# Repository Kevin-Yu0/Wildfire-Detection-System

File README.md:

# Wildfire-Detection-System
This is the codebase for the Wildfire Detection System Project
Computer Engineering Senior Capstone 2025-2026
Contributors:
    Kevin Yu
    Manny Lemus
    Jake Gilbert
    Aliston Ma
    Frank Xiao

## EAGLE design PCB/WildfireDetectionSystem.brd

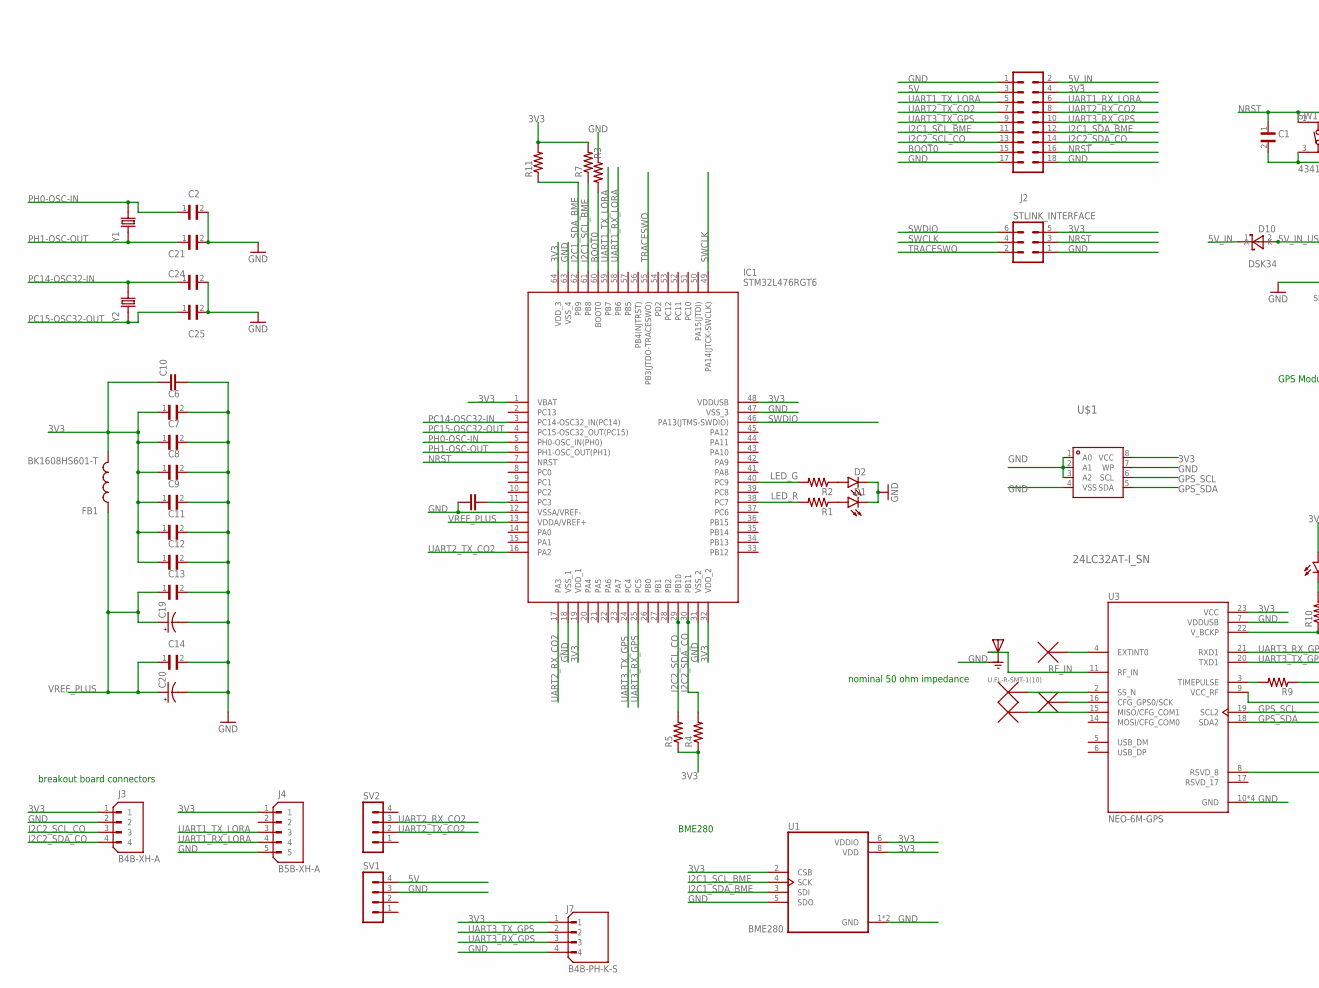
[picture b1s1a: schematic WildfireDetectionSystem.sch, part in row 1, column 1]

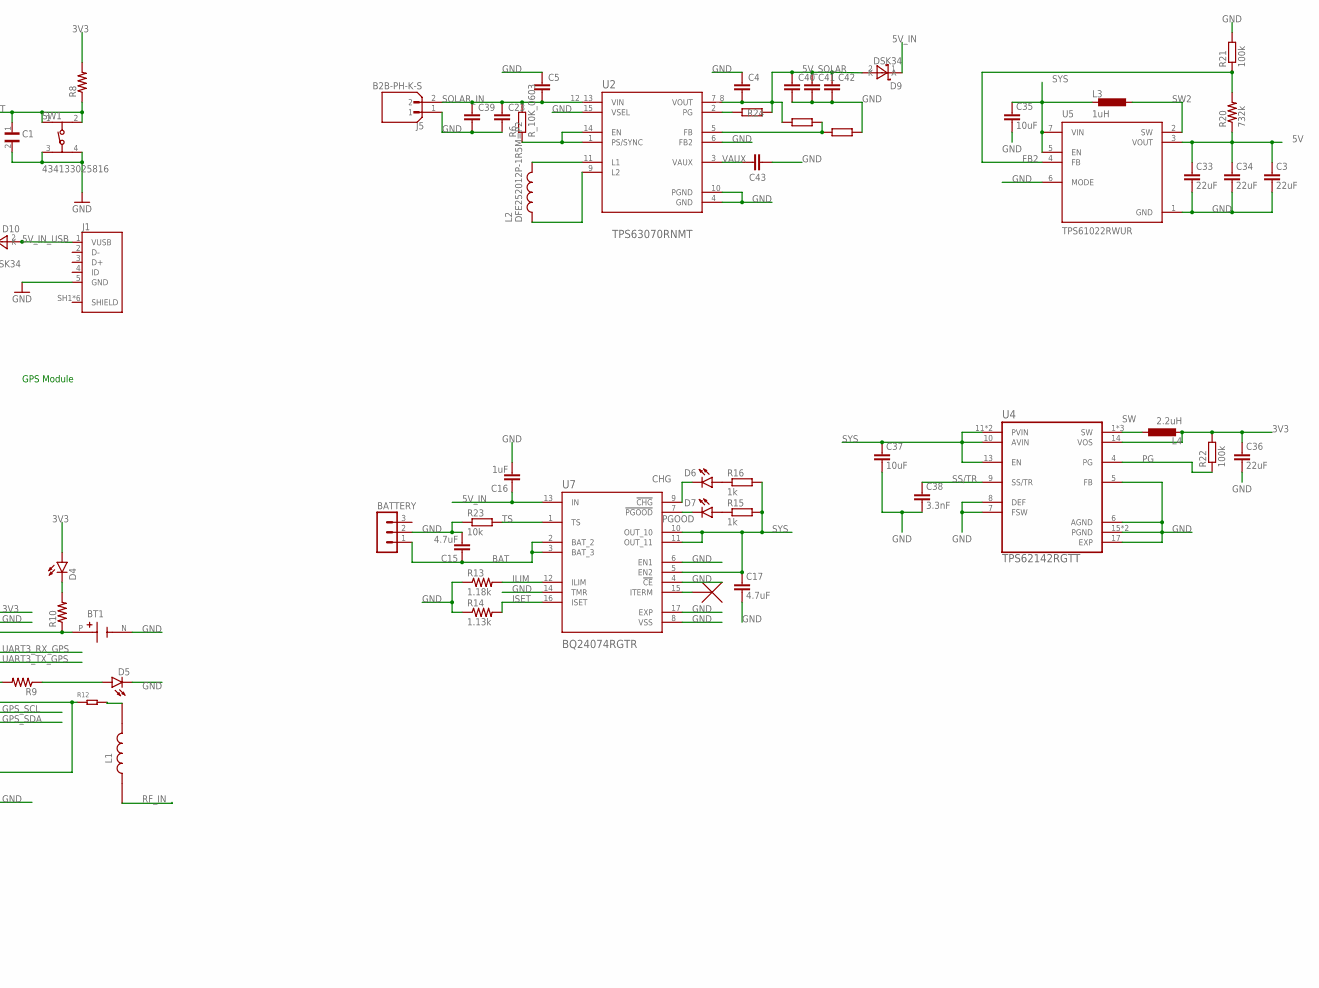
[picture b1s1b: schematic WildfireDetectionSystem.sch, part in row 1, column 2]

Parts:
BATTERY: MA03-1
BT1: 1056TR; BAT_1056TR
C1, C6, C7, C8, C9, C11, C12, C13, C14: CL05B104KO5NNNC; CAPC1005X55N
C2, C21, C24, C25: CL10C200JB8NNNC; CAPC1608X90N
C3, C33, C34, C36: 22uF; C0603
C4, C5: C_10UF/10V_0603; C0603
C10, C22: CC0603KRX5R7BB105; CAPC1608X90
C15, C17: 4.7uF; C0603
C16: 1uF; C0603
C19, C20: TAJA105K016RNJ; CAPPM3216X180N
C23, C39: C_10UF/25V_0805; C0805
C35, C37: 10uF; C0603
C38: 3.3nF; C0603
C40, C41, C42: C_22UF/25V_0805; C0805
C43: C_100NF/50V_0603; C0603
D1, D2, D5, D6: SML-P12MTT86; LED_SML-P11UTT86R
D4, D7: SML-P12VTT86; LED_SML-P11UTT86R
D9, D10: DSK34; SOD-123_L2.8-W1.8-LS3.7-RD
FB1: BK1608HS601-T; BEADC1608X95N
IC1: STM32L476RGT6; QFP50P1200X1200X160-64N
J1: 10118192-0001LF; AMPHENOL_10118192-0001LF
J2: MA09-2
J3: B4B-XH-A; JST_B4B-XH-A
J4: B5B-XH-A; JST_B5B-XH-A
J5: B2B-PH-K-S; JST_B2B-PH-K-S
J7: B4B-PH-K-S; JST_B4B-PH-K-S
J8: U.FL-R-SMT-1(10); HRS_U.FL-R-SMT-1(10)
L1: MLZ2012P220WT000; INDC2012X145N
L2: DFE252012P-1R5M=P2; INDC2520X120N
L3: 1uH; R0805
L4: 2.2uH; R0805
R1, R2, R3, R4, R5, R9, R10: RC0402FR-071KL; RESC1005X40N
R6: R_10K_0603; R0603
R7, R11: RT0402FRE074K7L; RESC1005X35N
R8: RC0402FR-0710KL; RESC1005X40N
R12: SMD-RES-22R-1%-1/16W(0402); R0402
R13: 1.18k; R0603; LCSC_PART C861193
R14: 1.13k; R0603; LCSC_PART C137782
R15, R16: 1k; R0603
R20: 732k; R0603; LCSC_PART C403344
R21, R22: 100k; R0603
R23: 10k; R0603
R24: R_100K_0603; R0603
R25: R_680K_0603; R0603
R26: R_130K_0603; R0603
STLINK_INTERFACE: MA03-2
SV1, SV2: MA04-1
SW1: 434133025816
U1: BME280; PSON65P250X250X100-8N
U2: TPS63070RNMT; VREG_TPS63070RNMT
U3: NEO-6M-GPS; XCVR_NEO-6M-GPS
U4: TPS62142RGTT; QFN50P300X300X100-17N
U5: TPS61022RWUR; CONV_TPS61022RWUR
U7: BQ24074RGTR; QFN50P300X300X100-17N
U$1: 24LC32AT-I_SN; SOIC-8_L4.9-W3.9-P1.27-LS6.0-BL
Y1: ABLS-8.000MHZ-B2-T; XTAL_ABLS-8.000MHZ-B2-T
Y2: ECS-.327-12.5-12QS-TR; XTAL_ECS-.327-12.5-12QS-TR

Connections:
3V3: C6.1, C7.1, C8.1, C9.1, C10.1, C11.1, C12.1, C36.1, D4.A, FB1.2, IC1.1 (VBAT), IC1.19 (VDD_1), IC1.32 (VDD_2), IC1.48 (VDDUSB), IC1.64 (VDD_3), J2.4, J3.1, J4.1, J7.1, L4.2, R4.1, R5.1, R7.2, R8.2, R11.2, R22.2, STLINK_INTERFACE.5, U1.2 (CSB), U1.6 (VDDIO), U1.8 (VDD), U3.23 (VCC), U4.14 (VOS), U$1.8 (VCC)
5V: C3.1, C33.1, C34.1, J2.3, R20.1, SV1.4, U5.3 (VOUT)
5V_IN: C16.1, D9.1 (K), D10.1 (K), J2.2, U7.13 (IN)
5V_IN_USB: D10.2 (A), J1.1 (VUSB)
5V_SOLAR: C4.2, C40.1, C41.1, C42.1, D9.2 (A), R24.2, R25.1, U2.7_8 (VOUT)
BAT: BATTERY.1, C15.1, U7.2 (BAT_2), U7.3 (BAT_3)
BOOT0: IC1.60 (BOOT0), J2.15, R3.2
CHG: D6.C, U7.9 (!CHG)
FB2: R20.2, R21.1, U5.4 (FB)
GND: BATTERY.2, BT1.N (NEG), C1.2, C2.2, C3.2, C4.1, C5.1, C6.2, C7.2, C8.2, C9.2, C10.2, C11.2, C12.2, C13.2, C14.2, C15.2, C16.2, C17.2, C19.C (-), C20.C (-), C21.2, C22.1, C23.2, C24.2, C25.2, C33.2, C34.2, C35.2, C36.2, C37.2, C38.2, C39.2, C40.2, C41.2, C42.2, C43.2, D1.C, D2.C, D5.C, IC1.12 (VSSA/VREF-), IC1.18 (VSS_1), IC1.31 (VSS_2), IC1.47 (VSS_3), IC1.63 (VSS_4), J1.5 (GND), J2.1, J2.17, J2.18, J3.2, J4.5, J5.1, J7.4, J8.1 (GND), J8.3 (GND), R3.1, R13.1, R14.1, R21.2, R23.1, R26.1, STLINK_INTERFACE.1, SV1.3, SW1.3, SW1.4, U1.1 (GND), U1.5 (SDO), U1.7 (GND), U2.4 (GND), U2.6 (FB2), U2.10 (PGND), U2.15 (VSEL), U3.7 (VDDUSB), U3.10 (GND), U3.12 (GND), U3.13 (GND), U3.24 (GND), U4.5 (FB), U4.6 (AGND), U4.7 (FSW), U4.8 (DEF), U4.15 (PGND), U4.16 (PGND), U4.17 (EXP), U5.1 (GND), U5.6 (MODE), U7.4 (!CE), U7.6 (EN1), U7.8 (VSS), U7.14 (TMR), U7.17 (EXP), U$1.1 (A0), U$1.2 (A1), U$1.3 (A2), U$1.4 (VSS), U$1.7 (WP)
GPS_SCL: U3.19 (SCL2), U$1.6 (SCL)
GPS_SDA: U3.18 (SDA2), U$1.5 (SDA)
I2C1_SCL_BME: IC1.61 (PB8), J2.11, R7.1, U1.4 (SCK)
I2C1_SDA_BME: IC1.62 (PB9), J2.12, R11.1, U1.3 (SDI)
I2C2_SCL_CO: IC1.29 (PB10), J2.13, J3.3, R5.2
I2C2_SDA_CO: IC1.30 (PB11), J2.14, J3.4, R4.2
ILIM: R13.2, U7.12 (ILIM)
ISET: R14.2, U7.16 (ISET)
LED_G: IC1.40 (PC9), R2.2
LED_R: IC1.38 (PC7), R1.2
unnamed: D1.A, R1.1
unnamed: R9.2, U3.3 (TIMEPULSE)
unnamed: D2.A, R2.1
unnamed: C22.2, IC1.11 (PC3)
unnamed: D4.C, R10.2
unnamed: R12.1, U3.8 (RSVD_8), U3.9 (VCC_RF)
unnamed: L1.2, R12.2
unnamed: BT1.P (POS), R10.1, U3.22 (V_BCKP)
unnamed: D5.A, R9.1
unnamed: D6.A, R16.1
unnamed: D7.A, R15.1
unnamed: L2.2, U2.11 (L1)
unnamed: L2.1, U2.9 (L2)
unnamed: R6.1, U2.1 (PS/SYNC), U2.14 (EN)
unnamed: R24.1, U2.2 (PG)
unnamed: R25.2, R26.2, U2.5 (FB)
NRST: C1.1, IC1.7 (NRST), J2.16, R8.1, STLINK_INTERFACE.3, SW1.1, SW1.2
PC14-OSC32-IN: C24.1, IC1.3 (PC14-OSC32_IN(PC14)), Y2.2
PC15-OSC32-OUT: C25.1, IC1.4 (PC15-OSC32_OUT(PC15)), Y2.1
PG: R22.1, U4.4 (PG)
PGOOD: D7.C, U7.7 (!PGOOD)
PH0-OSC-IN: C2.1, IC1.5 (PH0-OSC_IN(PH0)), Y1.2
PH1-OSC-OUT: C21.1, IC1.6 (PH1-OSC_OUT(PH1)), Y1.1
RF_IN: J8.2 (SIG), L1.1, U3.11 (RF_IN)
SOLAR_IN: C5.2, C23.1, C39.1, J5.2, R6.2, U2.12_13 (VIN)
SS/TR: C38.1, U4.9 (SS/TR)
SW: L4.1, U4.1 (SW), U4.2 (SW), U4.3 (SW)
SW2: L3.1, U5.2 (SW)
SWCLK: IC1.49 (PA14(JTCK-SWCLK)), STLINK_INTERFACE.4
SWDIO: IC1.46 (PA13(JTMS-SWDIO)), STLINK_INTERFACE.6
SYS: C17.1, C35.1, C37.1, L3.2, R15.2, R16.2, U4.10 (AVIN), U4.11 (PVIN), U4.12 (PVIN), U4.13 (EN), U5.5 (EN), U5.7 (VIN), U7.5 (EN2), U7.10 (OUT_10), U7.11 (OUT_11)
TRACESWO: IC1.55 (PB3(JTDO-TRACESWO)), STLINK_INTERFACE.2
TS: R23.2, U7.1 (TS)
UART1_RX_LORA: IC1.58 (PB6), J2.6, J4.4
UART1_TX_LORA: IC1.59 (PB7), J2.5, J4.3
UART2_RX_CO2: IC1.17 (PA3), J2.8, SV2.3
UART2_TX_CO2: IC1.16 (PA2), J2.7, SV2.2
UART3_RX_GPS: IC1.25 (PC5), J2.10, J7.3, U3.21 (RXD1)
UART3_TX_GPS: IC1.24 (PC4), J2.9, J7.2, U3.20 (TXD1)
VAUX: C43.1, U2.3 (VAUX)
VREF_PLUS: C13.1, C14.1, C19.A (+), C20.A (+), FB1.1, IC1.13 (VDDA/VREF+)

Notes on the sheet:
breakout board connectors
GPS Module
BME280
nominal 50 ohm impedance

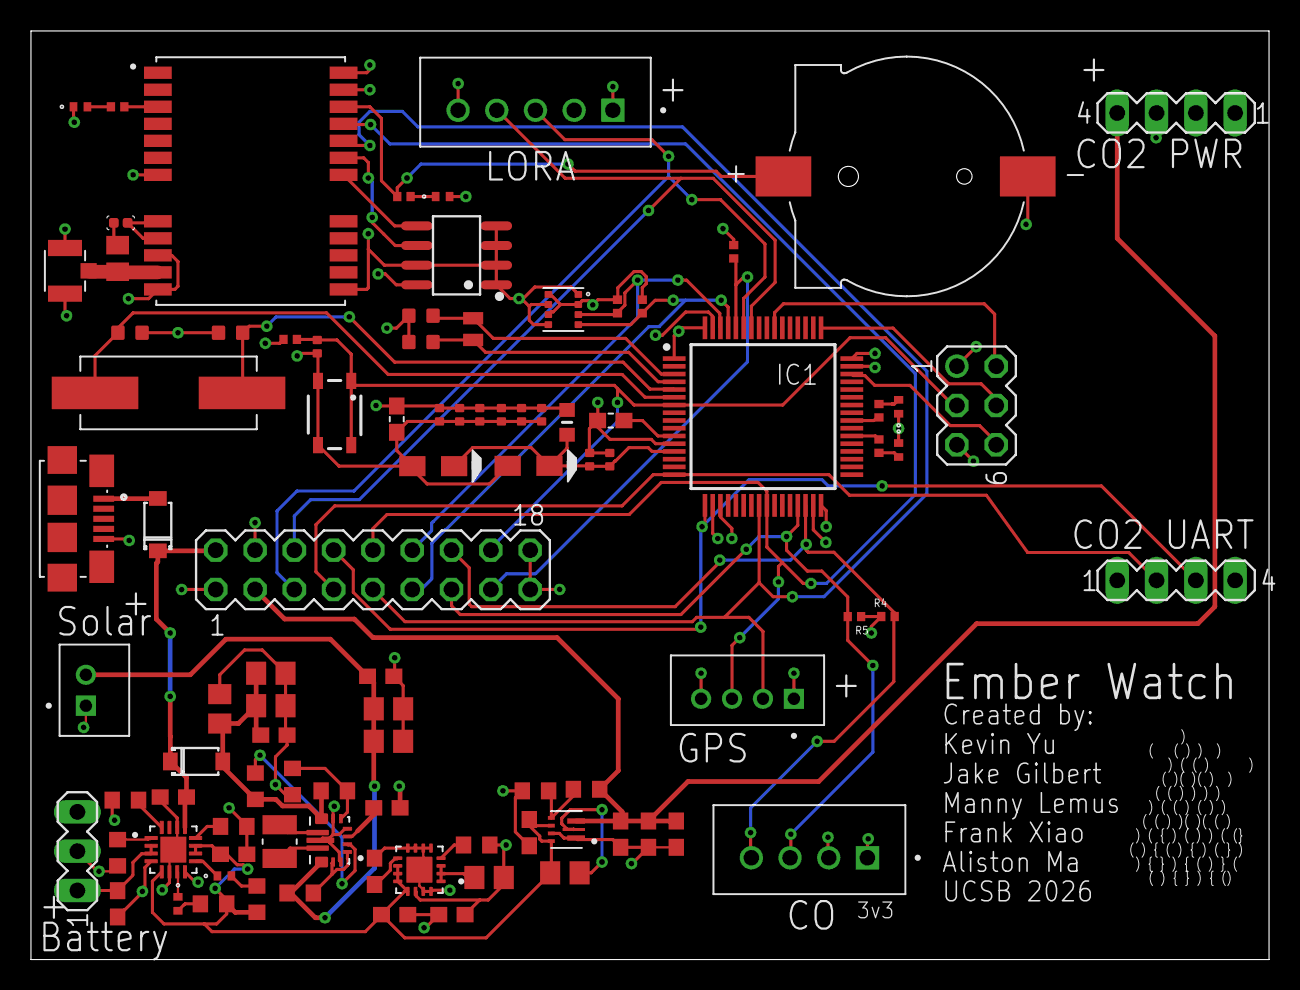
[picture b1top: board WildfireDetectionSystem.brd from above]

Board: 4 copper layers, 80.0 x 60.0 mm, 94 parts (0 on the bottom side), 61 nets.

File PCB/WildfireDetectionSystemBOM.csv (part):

"Part";"Value";"Device";"Package";"Description";"ALLIED_NUMBER";"ALLIED_PRICE-STOCK";"ARROW_PART_NUMBER";"ARROW_PRICE-STOCK";"AVAILABILITY";"CHECK_PRICES";"DESCRIPTION";"DIGI-KEY_PART_NUMBER";"DIGI-KEY_PURCHASE_URL";"DIGIKEY_PART_NUMBER";"HEIGHT";"LCSC_DATASHEET";"LCSC_PART";"LCSC_PRICE1_EUR";"LCSC_ROTATION_CCW";"LCSC_STOCK";"MANUFACTURER_NAME";"MANUFACTURER_PART_NUMBER";"MF";"MOUSER_PART_NUMBER";"MOUSER_PRICE-STOCK";"MP";"MPN";"OC_FARNELL";"OC_LCSC";"OC_NEWARK";"PACKAGE";"POPULARITY";"PRICE";"PROPERTIES";"PURCHASE-URL";"RS_PART_NUMBER";"RS_PRICE-STOCK";"SNAPEDA_LINK";"SPICEPREFIX";
"BATTERY";"";"MA03-1";"MA03-1";"PIN HEADER";"";"";"";"";"";"";"";"";"";"";"";"";"";"";"";"";"";"";"";"";"";"";"";"unknown";"";"unknown";"";"48";"";"";"";"";"";"";"";
"BT1";"1056TR";"1056TR";"BAT_1056TR";"Check availability";"";"";"";"";"In Stock";"https://www.snapeda.com/parts/1056TR/Keystone/view-part/?ref=eda";"                                                      SMT Holder for 12mm Cell-on Tape & Reel | Keystone Electronics 1056TR                                              ";"";"";"";"";"";"";"";"";"";"";"";"Keystone Electronics";"";"";"1056TR";"";"";"";"";"None";"";"None";"";"";"";"";"https://www.snapeda.com/parts/1056TR/Keystone/view-part/?ref=snap";"";
"C1";"CL05B104KO5NNNC";"CL05B104KO5NNNC";"CAPC1005X55N";"";"";"";"";"";"";"https://www.snapeda.com/parts/CL05B104KO5NNNC/Samsung/view-p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";"                                                      0.1 µF ±10% 16V Ceramic Capacitor X7R 0402 (1005 Metric)                                              ";"";"";"1276-1001-1-ND";"";"";"";"";"";"";"";"";"Samsung";"";"";"CL05B104KO5NNNC";"";"";"";"";"SMD-2 Samsung";"";"";"";"";"";"";"https://www.snapeda.com/parts/CL05B104KO5NNNC/Samsung/view-p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";"";
"C2";"CL10C200JB8NNNC";"CL10C200JB8NNNC";"CAPC1608X90N";"";"";"";"";"";"";"https://www.snapeda.com/parts/CL10C200JB8NNNC/Samsung/view-p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";"                                                      20 pF ±5% 50V Ceramic Capacitor C0G, NP0 0603 (1608 Metric)                                              ";"";"";"1276-1187-1-ND";"";"";"";"";"";"";"";"";"Samsung";"";"";"CL10C200JB8NNNC";"";"";"";"";"SMD-2 Samsung";"";"";"";"";"";"";"https://www.snapeda.com/parts/CL10C200JB8NNNC/Samsung/view-p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";"";
"C3";"22uF";"C_22UF/6.3V_0603";"C0603";"Capacitor General purpose SMD Capacitor";"";"";"";"";"";"";"";"";"";"";"";"https://datasheet.lcsc.com/lcsc/1811151138_Samsung-Electro-M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";"C59461";"";"0";"6685052";"";"";"";"";"";"";"";"";"";"";"";"";"";"6.3V 22uF X5R ±20% 0603  ROHS";"";"";"";"";"";
"C4";"C_10UF/10V_0603";"C_10UF/10V_0603";"C0603";"Capacitor General purpose SMD Capacitor";"";"";"";"";"";"";"";"";"";"";"";"https://datasheet.lcsc.com/lcsc/1810191219_Samsung-Electro-M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";"C19702";"";"0";"2089400";"";"";"";"";"";"";"";"";"";"";"";"";"";"10V 10uF X5R ±10% 0603  ROHS";"";"";"";"";"";
"C5";"C_10UF/10V_0603";"C_10UF/10V_0603";"C0603";"Capacitor General purpose SMD Capacitor";"";"";"";"";"";"";"";"";"";"";"";"https://datasheet.lcsc.com/lcsc/1810191219_Samsung-Electro-M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";"C19702";"";"0";"2089400";"";"";"";"";"";"";"";"";"";"";"";"";"";"10V 10uF X5R ±10% 0603  ROHS";"";"";"";"";"";
"C6";"CL05B104KO5NNNC";"CL05B104KO5NNNC";"CAPC1005X55N";"";"";"";"";"";"";"https://www.snapeda.com/parts/CL05B104KO5NNNC/Samsung/view-p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";"                                                      0.1 µF ±10% 16V Ceramic Capacitor X7R 0402 (1005 Metric)                                              ";"";"";"1276-1001-1-ND";"";"";"";"";"";"";"";"";"Samsung";"";"";"CL05B104KO5NNNC";"";"";"";"";"SMD-2 Samsung";"";"";"";"";"";"";"https://www.snapeda.com/parts/CL05B104KO5NNNC/Samsung/view-p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";"";
"C7";"CL05B104KO5NNNC";"CL05B104KO5NNNC";"CAPC1005X55N";"";"";"";"";"";"";"https://www.snapeda.com/parts/CL05B104KO5NNNC/Samsung/view-p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";"                                                      0.1 µF ±10% 16V Ceramic Capacitor X7R 0402 (1005 Metric)                                              ";"";"";"1276-1001-1-ND";"";"";"";"";"";"";"";"";"Samsung";"";"";"CL05B104KO5NNNC";"";"";"";"";"SMD-2 Samsung";"";"";"";"";"";"";"https://www.snapeda.com/parts/CL05B104KO5NNNC/Samsung/view-p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";"";
"C8";"CL05B104KO5NNNC";"CL05B104KO5NNNC";"CAPC1005X55N";"";"";"";"";"";"";"https://www.snapeda.com/parts/CL05B104KO5NNNC/Samsung/view-p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";"                                                      0.1 µF ±10% 16V Ceramic Capacitor X7R 0402 (1005 Metric)                                              ";"";"";"1276-1001-1-ND";"";"";"";"";"";"";"";"";"Samsung";"";"";"CL05B104KO5NNNC";"";"";"";"";"SMD-2 Samsung";"";"";"";"";"";"";"https://www.snapeda.com/parts/CL05B104KO5NNNC/Samsung/view-p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";"";
"C9";"CL05B104KO5NNNC";"CL05B104KO5NNNC";"CAPC1005X55N";"";"";"";"";"";"";"https://www.snapeda.com/parts/CL05B104KO5NNNC/Samsung/view-p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";"                                                      0.1 µF ±10% 16V Ceramic Capacitor X7R 0402 (1005 Metric)                                              ";"";"";"1276-1001-1-ND";"";"";"";"";"";"";"";"";"Samsung";"";"";"CL05B104KO5NNNC";"";"";"";"";"SMD-2 Samsung";"";"";"";"";"";"";"https://www.snapeda.com/parts/CL05B104KO5NNNC/Samsung/view-p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";"";
"C10";"CC0603KRX5R7BB105";"CC0603KRX5R7BB105";"CAPC1608X90";"CAPACITOR CERAMIC, 1µF, 10V, X5R, 0603; Dielectric Characteristic:X5R; Capacitance:1µF; Capacitance Tolerance:± 10%; Voltage Rating:16V; Temperature Coefficient:± 15%; Capacitor Case Style:0603; No. of Pins:2; Mounting Type:SMD ;RoHS Compliant: Yes";"";"";"";"";"";"";" 1µF ±10% 16V Ceramic Capacitor X5R 0603 _1608 Metric_ ";"311-1444-1-ND";"https://www.digikey.com/product-detail/en/yageo/CC0603KRX5R7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";"";"";"";"";"";"";"";"";"";"Yageo";"";"";"CC0603KRX5R7BB105";"";"";"";"";"0603 Yageo";"";"";"";"";"";"";"";"";
"C11";"CL05B104KO5NNNC";"CL05B104KO5NNNC";"CAPC1005X55N";"";"";"";"";"";"";"https://www.snapeda.com/parts/CL05B104KO5NNNC/Samsung/view-p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";"                                                      0.1 µF ±10% 16V Ceramic Capacitor X7R 0402 (1005 Metric)                                              ";"";"";"1276-1001-1-ND";"";"";"";"";"";"";"";"";"Samsung";"";"";"CL05B104KO5NNNC";"";"";"";"";"SMD-2 Samsung";"";"";"";"";"";"";"https://www.snapeda.com/parts/CL05B104KO5NNNC/Samsung/view-p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";"";
"C12";"CL05B104KO5NNNC";"CL05B104KO5NNNC";"CAPC1005X55N";"";"";"";"";"";"";"https://www.snapeda.com/parts/CL05B104KO5NNNC/Samsung/view-p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";"                                                      0.1 µF ±10% 16V Ceramic Capacitor X7R 0402 (1005 Metric)                                              ";"";"";"1276-1001-1-ND";"";"";"";"";"";"";"";"";"Samsung";"";"";"CL05B104KO5NNNC";"";"";"";"";"SMD-2 Samsung";"";"";"";"";"";"";"https://www.snapeda.com/parts/CL05B104KO5NNNC/Samsung/view-p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";"";
"C13";"CL05B104KO5NNNC";"CL05B104KO5NNNC";"CAPC1005X55N";"";"";"";"";"";"";"https://www.snapeda.com/parts/CL05B104KO5NNNC/Samsung/view-p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";"                                                      0.1 µF ±10% 16V Ceramic Capacitor X7R 0402 (1005 Metric)                                              ";"";"";"1276-1001-1-ND";"";"";"";"";"";"";"";"";"Samsung";"";"";"CL05B104KO5NNNC";"";"";"";"";"SMD-2 Samsung";"";"";"";"";"";"";"https://www.snapeda.com/parts/CL05B104KO5NNNC/Samsung/view-p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";"";
"C14";"CL05B104KO5NNNC";"CL05B104KO5NNNC";"CAPC1005X55N";"";"";"";"";"";"";"https://www.snapeda.com/parts/CL05B104KO5NNNC/Samsung/view-p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";"                                                      0.1 µF ±10% 16V Ceramic Capacitor X7R 0402 (1005 Metric)                                              ";"";"";"1276-1001-1-ND";"";"";"";"";"";"";"";"";"Samsung";"";"";"CL05B104KO5NNNC";"";"";"";"";"SMD-2 Samsung";"";"";"";"";"";"";"https://www.snapeda.com/parts/CL05B104KO5NNNC/Samsung/view-p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";"";
"C15";"4.7uF";"C_4.7PF/50V_0603";"C0603";"Capacitor General purpose SMD Capacitor";"";"";"";"";"";"";"";"";"";"";"";"https://datasheet.lcsc.com/lcsc/1810261624_FH-Guangdong-Feng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";"C1669";"";"0";"1338830";"";"";"";"";"";"";"";"";"";"";"";"";"";"50V 4.7pF C0G ±0.25pF 0603  ROHS";"";"";"";"";"";
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
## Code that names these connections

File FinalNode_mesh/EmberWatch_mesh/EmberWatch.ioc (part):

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Mcu.Name=STM32L476R(C-E-G)Tx
Mcu.Package=LQFP64
Mcu.UserName=STM32L476RGTx
PA2.Mode=Asynchronous
PA2.Signal=USART2_TX
PA3.Mode=Asynchronous
PA3.Signal=USART2_RX
PB10.Mode=I2C
PB10.Signal=I2C2_SCL
PB11.Mode=I2C
PB11.Signal=I2C2_SDA
PB6.Mode=Asynchronous
PB6.Signal=USART1_TX
PB7.Mode=Asynchronous
PB7.Signal=USART1_RX
PB8.Mode=I2C
PB8.Signal=I2C1_SCL
PB9.Mode=I2C
PB9.Signal=I2C1_SDA
PC14-OSC32_IN\ (PC14).Mode=LSE-External-Oscillator
PC14-OSC32_IN\ (PC14).Signal=RCC_OSC32_IN
PC15-OSC32_OUT\ (PC15).Mode=LSE-External-Oscillator
PC15-OSC32_OUT\ (PC15).Signal=RCC_OSC32_OUT
PC4.Mode=Asynchronous
PC4.Signal=USART3_TX
PC5.Mode=Asynchronous
PC5.Signal=USART3_RX
PC7.Signal=GPIO_Output
PC9.Signal=GPIO_Output
PH0-OSC_IN\ (PH0).Mode=HSE-External-Oscillator
PH0-OSC_IN\ (PH0).Signal=RCC_OSC_IN
PH1-OSC_OUT\ (PH1).Mode=HSE-External-Oscillator
PH1-OSC_OUT\ (PH1).Signal=RCC_OSC_OUT
RCC.HSE_VALUE=8000000
RCC.SYSCLKFreq_VALUE=80000000
RCC.SYSCLKSource=RCC_SYSCLKSOURCE_PLLCLK
board=custom

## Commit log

2026-01-22 LoRa to Supabase
    This is the bridge between the LoRa receiver and Supabase.
    this script is a base station bridge that sits between two totally different interfaces: on one side it has a serial (UART) stream coming from the RYLR998 LoRa receiver (connected to laptop through R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
2026-01-27 Created folderstructure and pushed PCB schematic and Board
2026-01-28 edited board layout with comments from Kriteen
2026-01-29 clearance set to .1mm
2026-01-29 Create lora_to_supabase.py
    This is the code required to send LoRa data output directly to supabase database
2026-01-29 Frank's models
2026-01-29 Model Training file updated
2026-01-29 code modifications
2026-01-29 Updated the model training
    Include Linear, KNN, and Random Forest
2026-02-05 Add LoRa → Supabase base station bridge with checksum validation and argparse support + a few minor changes, check script comments
2026-02-05 Train data from Supabase
2026-02-11 Replaced parts on PCB for JLC
2026-02-11 board and schematic changes
2026-02-12 probabilistic model
2026-02-19 webapp
2026-02-19 Renewed Model Training
2026-02-19 Renewed ML Model and Apply to Supabase
2026-02-19 Uploaded the trained model
2026-02-19 Delete FirePredictionModel/Linear_Classifier_Model_Training_Frank.ipynb
    Deleted outdated file
2026-02-19 Added code for model utilization
2026-03-07 Replace CSV payload parsing with packed binary decoding
2026-03-08 probabilistic model and manny's cm code
2026-03-14 updated packet structure and implemented communicaiton protocl
2026-04-10 ML: added hotkey to update firestatus on command
2026-04-10 pcb v2
2026-04-16 Another version of centralmonintoring system
    This one matches jake's main.c
2026-04-17 rebrand of whole website with time graph of webapp
2026-04-21 pcbv2
2026-04-23 changed charging circuit to add buck/boost
2026-04-23 inductor change
2026-04-24 data log
2026-04-30 added logic so receiver can upload to supabase
2026-04-30 Frank's new model
2026-05-01 Update README with dataset and processing details
    Added descriptions for dataset and processing scripts.
2026-05-01 Predict Fire risk of data inside Supabase
2026-05-01 Updated code applying model to Supabase data
    Updated README to reflect new model application and next steps.
2026-05-01 Update README with dataset and script details
    Added descriptions for datasets and processing scripts.
2026-05-08 modelv2
2026-05-08 Revised Model by Frank
2026-05-10 ML: added STM32 L476 node project and firmware
2026-05-10 ML removed manual fire override hotkey
2026-05-10 Update CenteralMonitoringSystem.py
    I literally only changed the name in the comment on line 2, from "lora_to_supabase.py" to "CenteralMonitoringSystem.py" to match the files name
2026-05-10 Update uart_recieve.py
    I literally only changed the comment on Line 2 from "hub_receiver.py" to "uart_recieve.py" to match the file name
2026-05-10 ML added a few updates, see description
2026-05-10 ml small CRC change
2026-05-10 ML added port & baud at the top
2026-05-11 Updated ACK payload length calculation & improved duplicate packet handling
2026-05-11 This main.c will now work with CentralMonitoringSystem.py
2026-05-11 Remove hardcoded Supabase credentials
2026-05-11 Update L476 node BME280 and CO sensor support
2026-05-11 Add LoRa RF power setup command
2026-05-12 added GPS code
2026-05-13 Delete CenteralMonitoringSystem2.py
    no longer needed
2026-05-14 changes webapp
2026-05-21 refactored node and cms
2026-05-22 cms multinode
2026-05-23 Add mesh node STM32 project
2026-05-25 Delete FinalNode_mesh/EmberWatch_mesh directory
    no longer needed
2026-05-27 Final EmberWatch updates
2026-05-28 Final version of training code
